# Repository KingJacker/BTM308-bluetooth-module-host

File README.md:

#  Host Board for BTM308 Bluetooth Audio Receiver

This is a carrier board for the BTM308 Bluetooth audio module.

## Schematic

### BTM308

### Differential OP-AMP (OPA1678)

### Board to Board Interface

## Layout

| Top | Inner 1 | Inner 2 | Bottom |
|---|---|---|---|
|  |   |  |  |

## Assembly

## Bill of Materials

| Designator		| Footprint								| Qty. 	| Designation		|
| --- 				| --- 									| ---	| --- 				|
| C4				| C_0805_2012Metric						| 1		| 100nF				|
| C8,C6,C7,C9		| C_0805_2012Metric						| 4		| 1uF				|
| C12,C13			| C_0805_2012Metric						| 2		| 10uf				|
| C5,C3,C10			| C_0805_2012Metric						| 3		| 22uF				|
| C11,C1,C2			| C_0805_2012Metric						| 3		| 220uF				|
| D1				| LED_0805_2012Metric					| 1		| BLUE				|
| D2				| LED_0805_2012Metric					| 1		| RED				|
| D3				| D_SMA									| 1		| SMAJ6.0A			|
| J1				| PinHeader_2x05_P2.54mm_Vertical		| 1		| Bottom			|
| J5				| PinHeader_2x05_P2.54mm_Vertical		| 1		| Top				|
| J2				| USB_C_Receptacle_HRO_TYPE-C-31-M-12	| 1		| USB_C_Receptacle_USB2.0_16P |
| R14,R21			| R_0805_2012Metric						| 2		| 0R / Ferrite Bead	|
| R2,R5,R1,R4,R3	| R_0805_2012Metric 					| 5		| 1k				|
| R17,R18			| R_0805_2012Metric 					| 2		| 5.1k				|
| R16,R9,R6,R7,R13,R10,R11,R15,R8,R12 | R_0805_2012Metric 	| 10	| 10k				|
| R20,R19			| R_0805_2012Metric 					| 2		| 47				|
| SW6,SW1,SW2,SW3	| TST-A002_0.6MM_BOSS					| 4		| Battery Status, PLAY, VOL+/-	|
| SW4				| SLW8645745ARAND						| 1		| ON/OFF			|
| U1				| BTM308								| 1		| Bluetooth Module	|
| U2				| SOIC-8_5.3x5.3mm_P1.27mm				| 1		| OPA1678 OP-AMP    |
| U3				| PJ-320A								| 1		| PJ-320A Audio     |

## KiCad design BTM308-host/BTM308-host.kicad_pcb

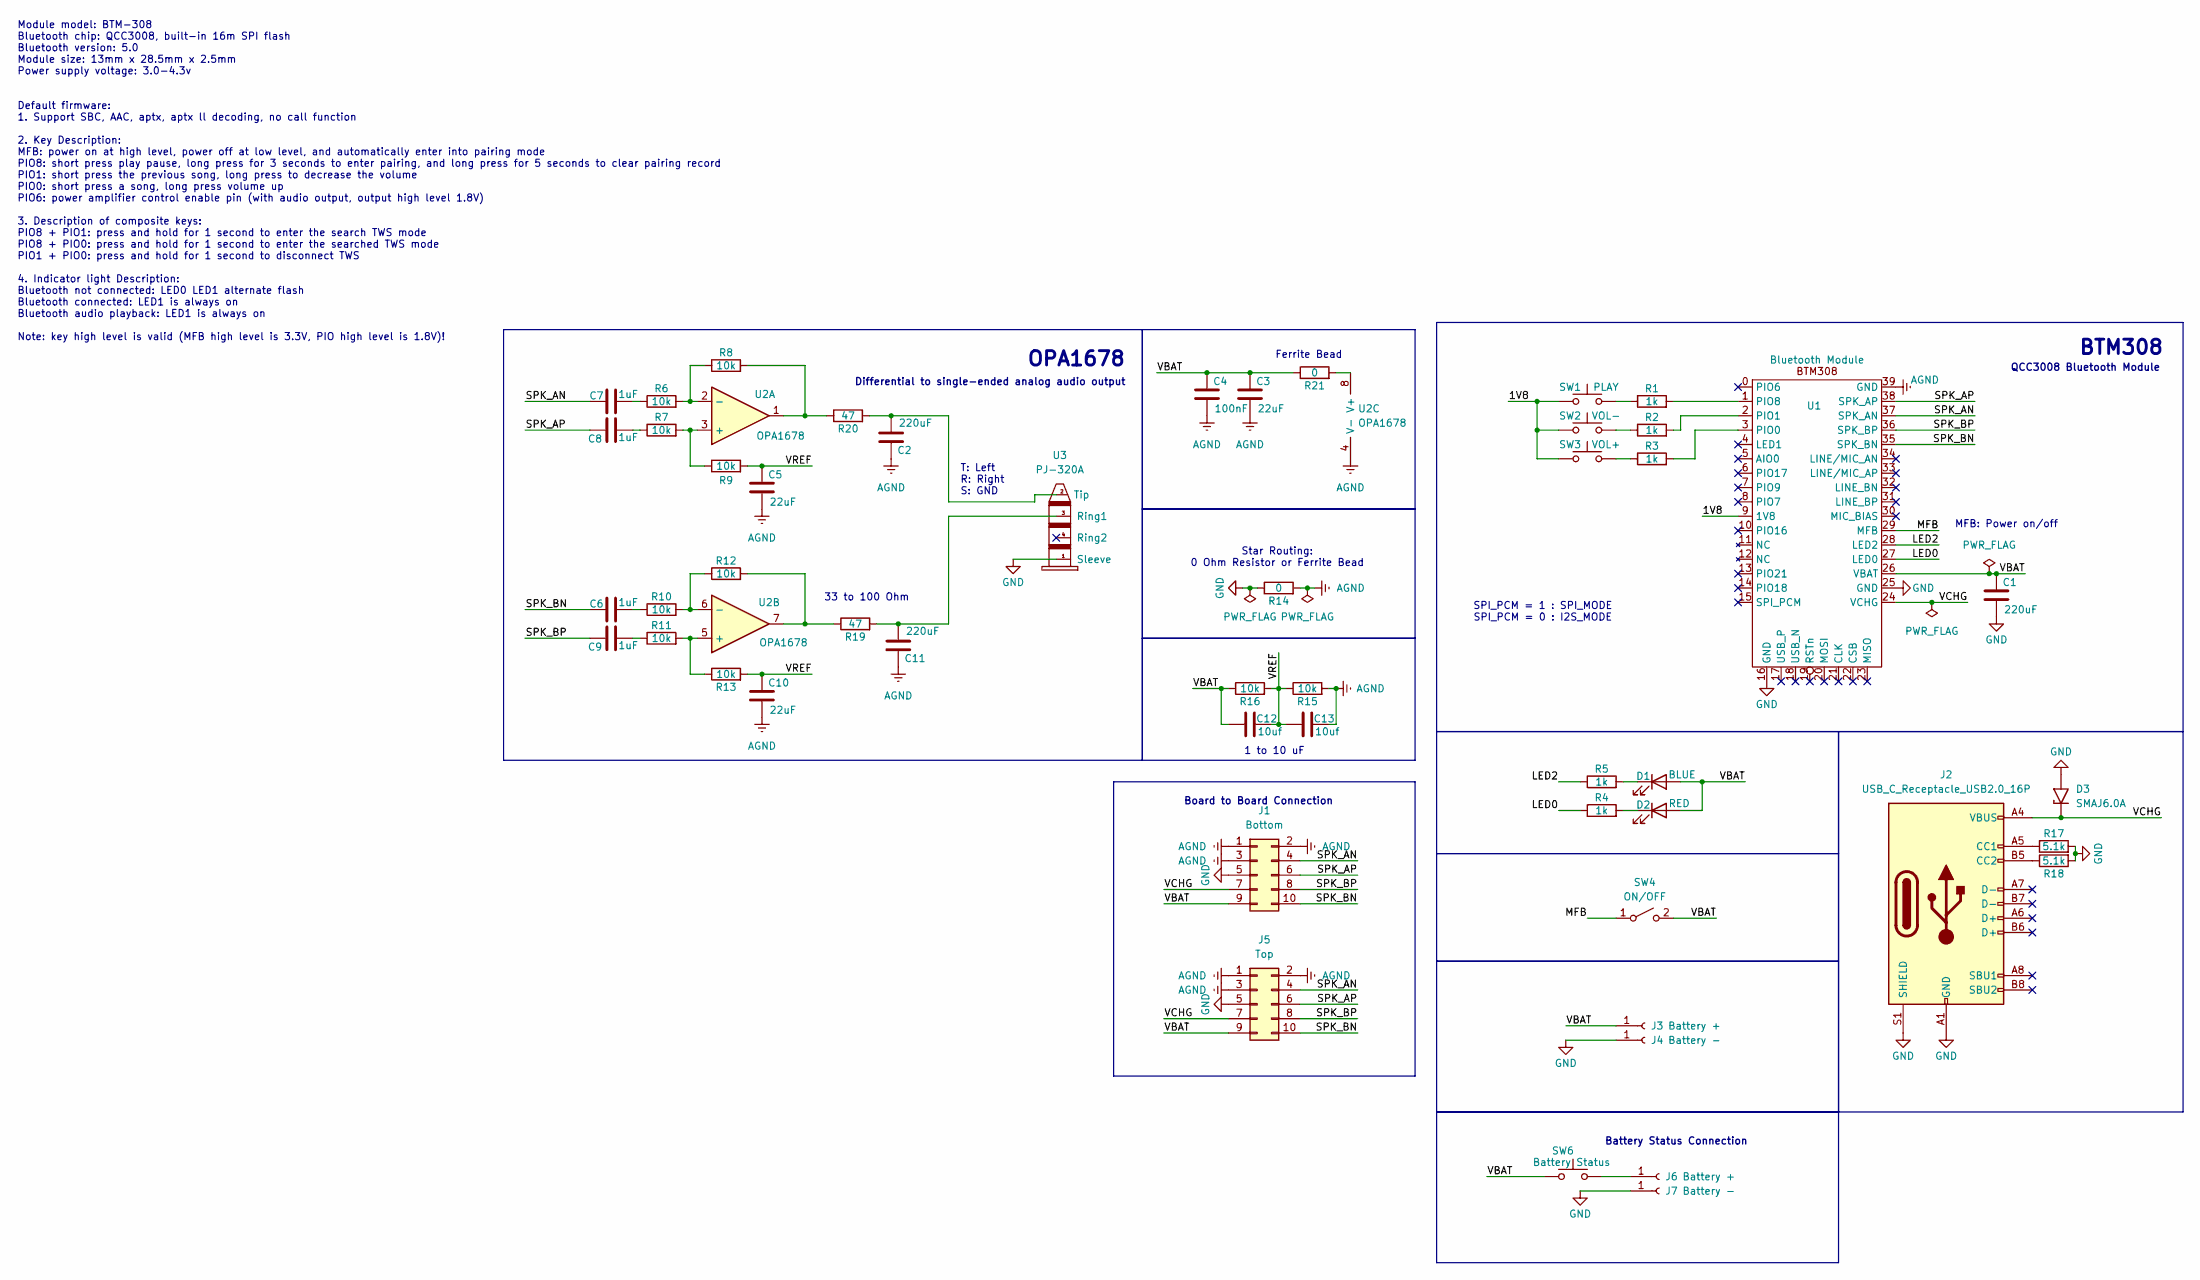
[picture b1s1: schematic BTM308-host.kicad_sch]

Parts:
C1, C2, C11: 220uF; C_0805_2012Metric_Pad1.18x1.45mm_HandSolder
C3, C5, C10: 22uF; C_0805_2012Metric_Pad1.18x1.45mm_HandSolder
C4: 100nF; C_0805_2012Metric_Pad1.18x1.45mm_HandSolder
C6, C7, C8, C9: 1uF; C_0805_2012Metric_Pad1.18x1.45mm_HandSolder
C12, C13: 10uf; C_0805_2012Metric_Pad1.18x1.45mm_HandSolder
D1: BLUE; LED_0805_2012Metric_Pad1.15x1.40mm_HandSolder
D2: RED; LED_0805_2012Metric_Pad1.15x1.40mm_HandSolder
D3: SMAJ6.0A; D_SMA
J1: Bottom; PinHeader_2x05_P2.54mm_Vertical
J2: USB_C_Receptacle_USB2.0_16P; USB_C_Receptacle_HRO_TYPE-C-31-M-12
J3, J6: Battery +; PinHeader_1x01_P2.54mm_Vertical
J4, J7: Battery -; PinHeader_1x01_P2.54mm_Vertical
J5: Top; PinHeader_2x05_P2.54mm_Vertical
R1, R2, R3, R4, R5: 1k; R_0805_2012Metric_Pad1.20x1.40mm_HandSolder
R6, R7, R8, R9, R10, R11, R12, R13, R15, R16: 10k; R_0805_2012Metric_Pad1.20x1.40mm_HandSolder
R14, R21: 0; R_0805_2012Metric_Pad1.20x1.40mm_HandSolder
R17, R18: 5.1k; R_0805_2012Metric_Pad1.20x1.40mm_HandSolder
R19, R20: 47; R_0805_2012Metric_Pad1.20x1.40mm_HandSolder
SW1: PLAY; TST-A002_0.6MM_BOSS
SW2: VOL-; TST-A002_0.6MM_BOSS
SW3: VOL+; TST-A002_0.6MM_BOSS
SW4: ON/OFF; SLW8645745ARAND
SW6: Battery Status; TST-A002_0.6MM_BOSS
U1: Bluetooth Module; BTM308
U2: OPA1678; SOIC-8_5.3x5.3mm_P1.27mm
U3: PJ-320A

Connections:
/1V8: SW1.1, SW2.1, SW3.1, U1.9 (1V8)
/LED0: R4.1, U1.27 (LED0)
/LED2: R5.1, U1.28 (LED2)
/MFB: SW4.1 (A), U1.29 (MFB)
/SPK_AN: C7.1, J1.4, J5.4, U1.37 (SPK_AN)
/SPK_AP: C8.1, J1.6, J5.6, U1.38 (SPK_AP)
/SPK_BN: C6.1, J1.10, J5.10, U1.35 (SPK_BN)
/SPK_BP: C9.1, J1.8, J5.8, U1.36 (SPK_BP)
/VBAT: C1.1, C3.1, C4.1, C12.2, D1.2 (A), D2.2 (A), J1.9, J3.1, J5.9, R16.1, R21.1, SW4.2 (B), SW6.1, U1.26 (VBAT)
/VCHG: D3.1 (A1), J1.7, J2.A4 (VBUS), J2.A9 (VBUS), J2.B4 (VBUS), J2.B9 (VBUS), J5.7, U1.24 (VCHG)
/VREF: C5.1, C10.1, C12.1, C13.2, R9.2, R13.2, R15.1, R16.2
AGND: C2.1, C3.2, C4.2, C5.2, C10.2, C11.1, C13.1, J1.1, J1.2, J1.3, J5.1, J5.2, J5.3, R14.2, R15.2, U1.39 (GND), U2.4 (V-)
GND: C1.2, D3.2 (A2), J1.5, J2.A1 (GND), J2.A12 (GND), J2.B1 (GND), J2.B12 (GND), J2.S1 (SHIELD), J4.1, J5.5, J7.1, R14.1, R17.2, R18.2, U1.16 (GND), U1.25 (GND), U3.1 (Sleeve)
unnamed: C6.2, R10.1
unnamed: C7.2, R6.1
unnamed: C8.2, R7.1
unnamed: C9.2, R11.1
unnamed: D1.1 (K), R5.2
unnamed: D2.1 (K), R4.2
unnamed: J2.A5 (CC1), R17.1
unnamed: J2.B5 (CC2), R18.1
unnamed: J6.1, SW6.2
unnamed: R1.1, SW1.2
unnamed: R2.1, SW2.2
unnamed: R3.1, SW3.2
unnamed: R12.2, R19.1, U2.7
unnamed: R8.2, R20.1, U2.1
unnamed: R3.2, U1.3 (PIO0)
unnamed: R2.2, U1.2 (PIO1)
unnamed: R1.2, U1.1 (PIO8)
unnamed: R7.2, R9.1, U2.3 (+)
unnamed: R6.2, R8.1, U2.2 (-)
unnamed: R11.2, R13.1, U2.5 (+)
unnamed: R10.2, R12.1, U2.6 (-)
unnamed: R21.2, U2.8 (V+)
unnamed: C11.2, R19.2, U3.3 (Ring1)
unnamed: C2.2, R20.2, U3.2 (Tip)

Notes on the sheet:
T: Left R: Right S: GND
Module model: BTM-308 Bluetooth chip: QCC3008, built-in 16m SPI flash Bluetooth version: 5.0 Module size: 13mm x 28.5mm x 2.5mm Power supply voltage: 3.0-4.3v Default firmware: 1. Support SBC, AAC, aptx, aptx ll decoding, no call function 2. Key Description: MFB: power on at high level, power off a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
SPI_PCM = 1 : SPI_MODE SPI_PCM = 0 : I2S_MODE
Differential to single-ended analog audio output
Board to Board Connection
BTM308
Battery Status Connection
MFB: Power on/off
QCC3008 Bluetooth Module
33 to 100 Ohm
1 to 10 uF
OPA1678
Ferrite Bead
Star Routing: 0 Ohm Resistor or Ferrite Bead

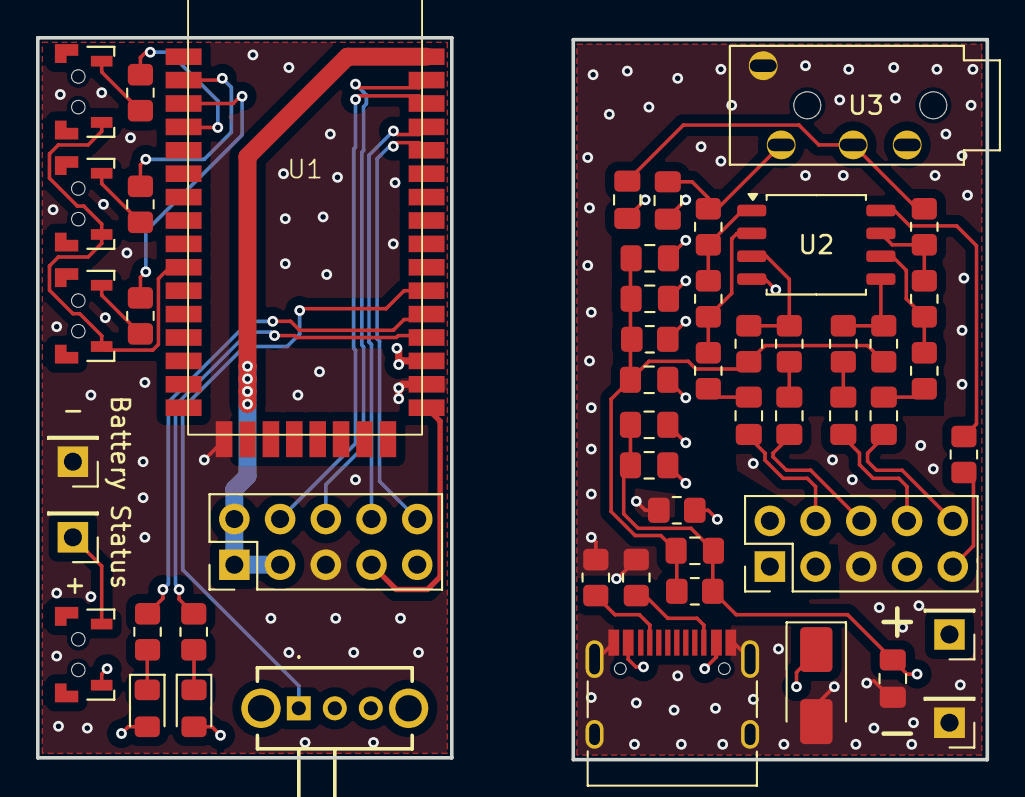
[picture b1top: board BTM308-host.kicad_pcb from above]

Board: 4 copper layers, 52.8 x 40.1 mm, 52 parts (0 on the bottom side), 37 nets.

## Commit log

2025-09-26 schematic finished
2025-09-27 layout position set
2025-09-27 layout done
2025-09-28 readme
2025-10-20 added fab
